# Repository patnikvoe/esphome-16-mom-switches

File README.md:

# esphome-16-mom-switches
create a pcb to be able to extend the use of homeassistant via esphome. Currently still a work in progress. Feedback welcome!

## components
- Seeedstudio Xiao ESP32C3
- MCP23017
- 10k resistor
- momentary push buttons
- array resistor
- 2x10 Male & Female header

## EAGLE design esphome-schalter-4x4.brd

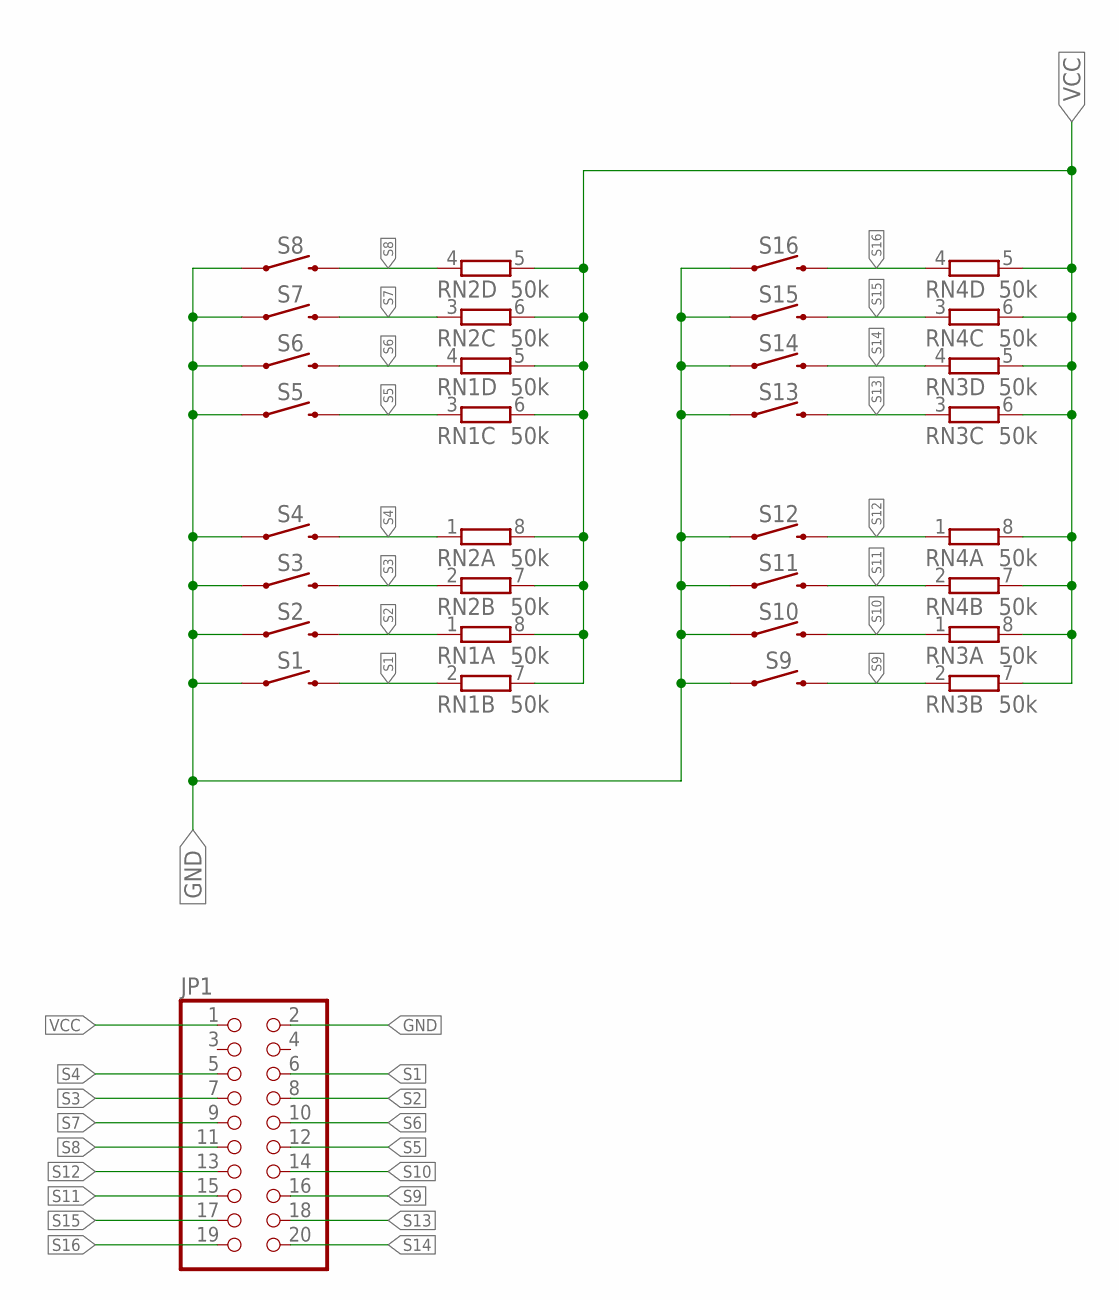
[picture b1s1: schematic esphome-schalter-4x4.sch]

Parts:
JP1: PINHD-2X10; 2X10
RN1, RN2, RN3, RN4: 50k; EXBS8V
S1, S2, S3, S4, S5, S6, S7, S8, S9, S10, S11, S12, S13, S14, S15, S16: MOMENTARY-SWITCH-SPST-PTH-6.0MM; TACTILE_SWITCH_PTH_6.0MM

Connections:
GND: JP1.2, S1.1, S2.1, S3.1, S4.1, S5.1, S6.1, S7.1, S8.1, S9.1, S10.1, S11.1, S12.1, S13.1, S14.1, S15.1, S16.1
S1: JP1.6, RN1.2 (1), S1.3 (2)
S2: JP1.8, RN1.1, S2.3 (2)
S3: JP1.7, RN2.2 (1), S3.3 (2)
S4: JP1.5, RN2.1, S4.3 (2)
S5: JP1.12, RN1.3 (1), S5.3 (2)
S6: JP1.10, RN1.4 (1), S6.3 (2)
S7: JP1.9, RN2.3 (1), S7.3 (2)
S8: JP1.11, RN2.4 (1), S8.3 (2)
S9: JP1.16, RN3.2 (1), S9.3 (2)
S10: JP1.14, RN3.1, S10.3 (2)
S11: JP1.15, RN4.2 (1), S11.3 (2)
S12: JP1.13, RN4.1, S12.3 (2)
S13: JP1.18, RN3.3 (1), S13.3 (2)
S14: JP1.20, RN3.4 (1), S14.3 (2)
S15: JP1.17, RN4.3 (1), S15.3 (2)
S16: JP1.19, RN4.4 (1), S16.3 (2)
VCC: JP1.1, RN1.5 (2), RN1.6 (2), RN1.7 (2), RN1.8 (2), RN2.5 (2), RN2.6 (2), RN2.7 (2), RN2.8 (2), RN3.5 (2), RN3.6 (2), RN3.7 (2), RN3.8 (2), RN4.5 (2), RN4.6 (2), RN4.7 (2), RN4.8 (2)

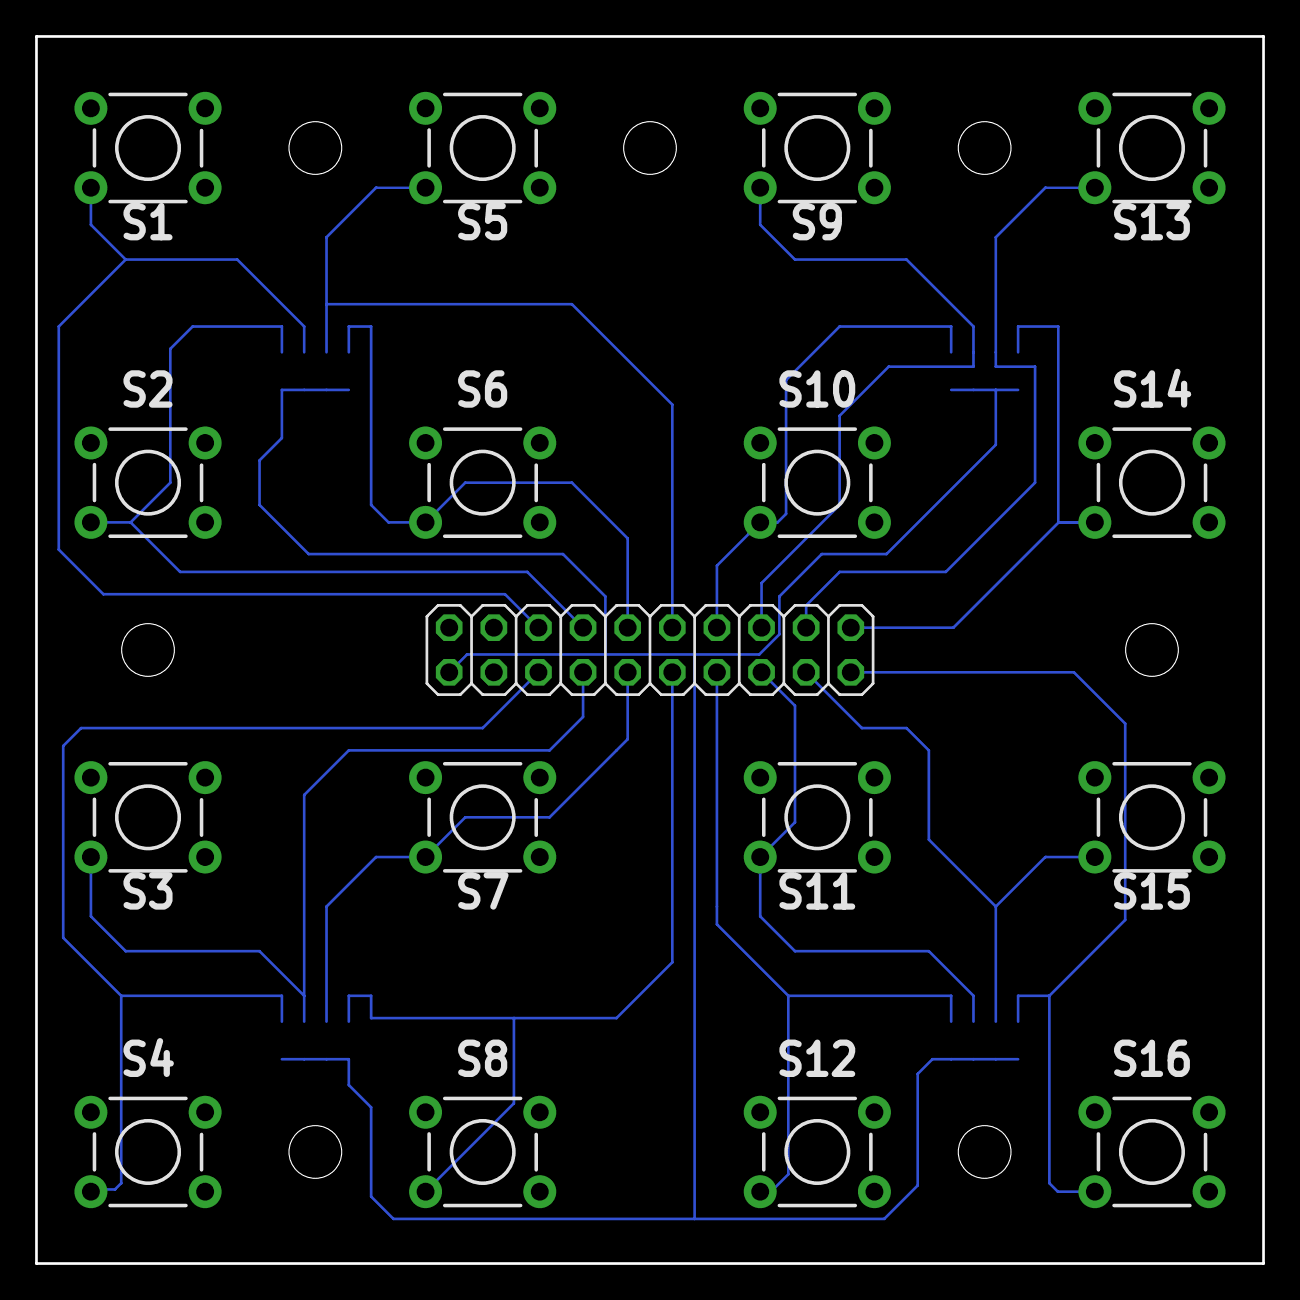
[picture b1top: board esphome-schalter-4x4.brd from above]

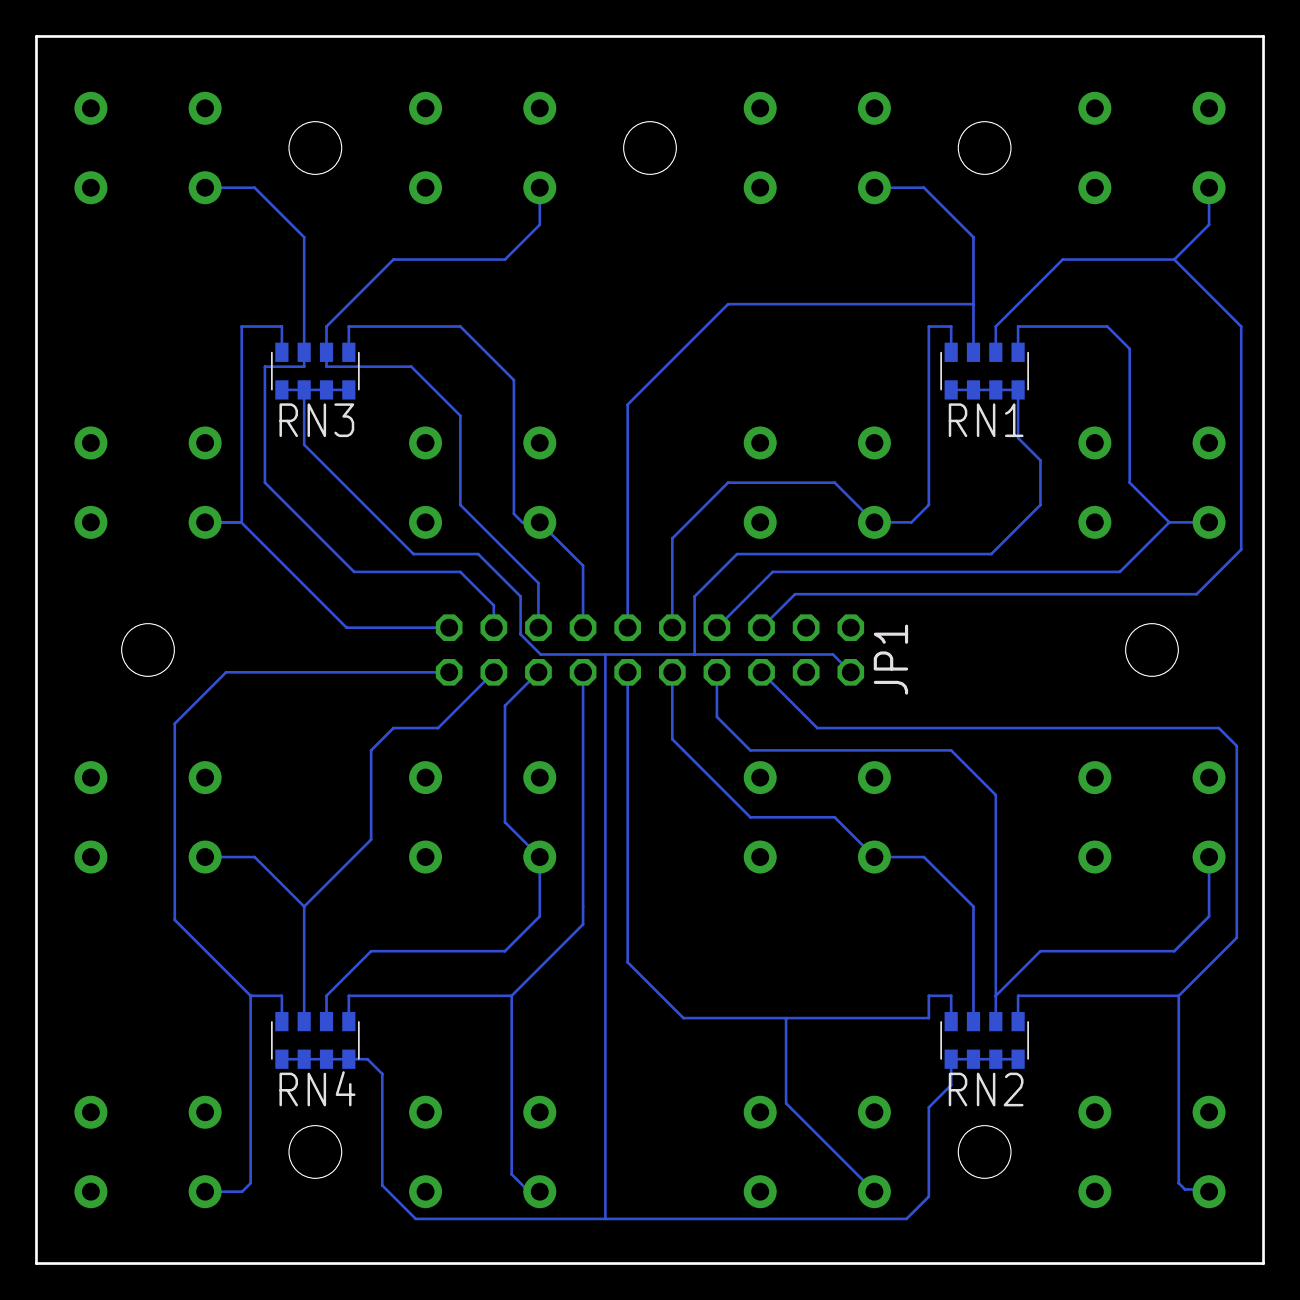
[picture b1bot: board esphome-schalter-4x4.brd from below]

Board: 2 copper layers, 69.8 x 69.8 mm, 21 parts (4 on the bottom side), 18 nets.

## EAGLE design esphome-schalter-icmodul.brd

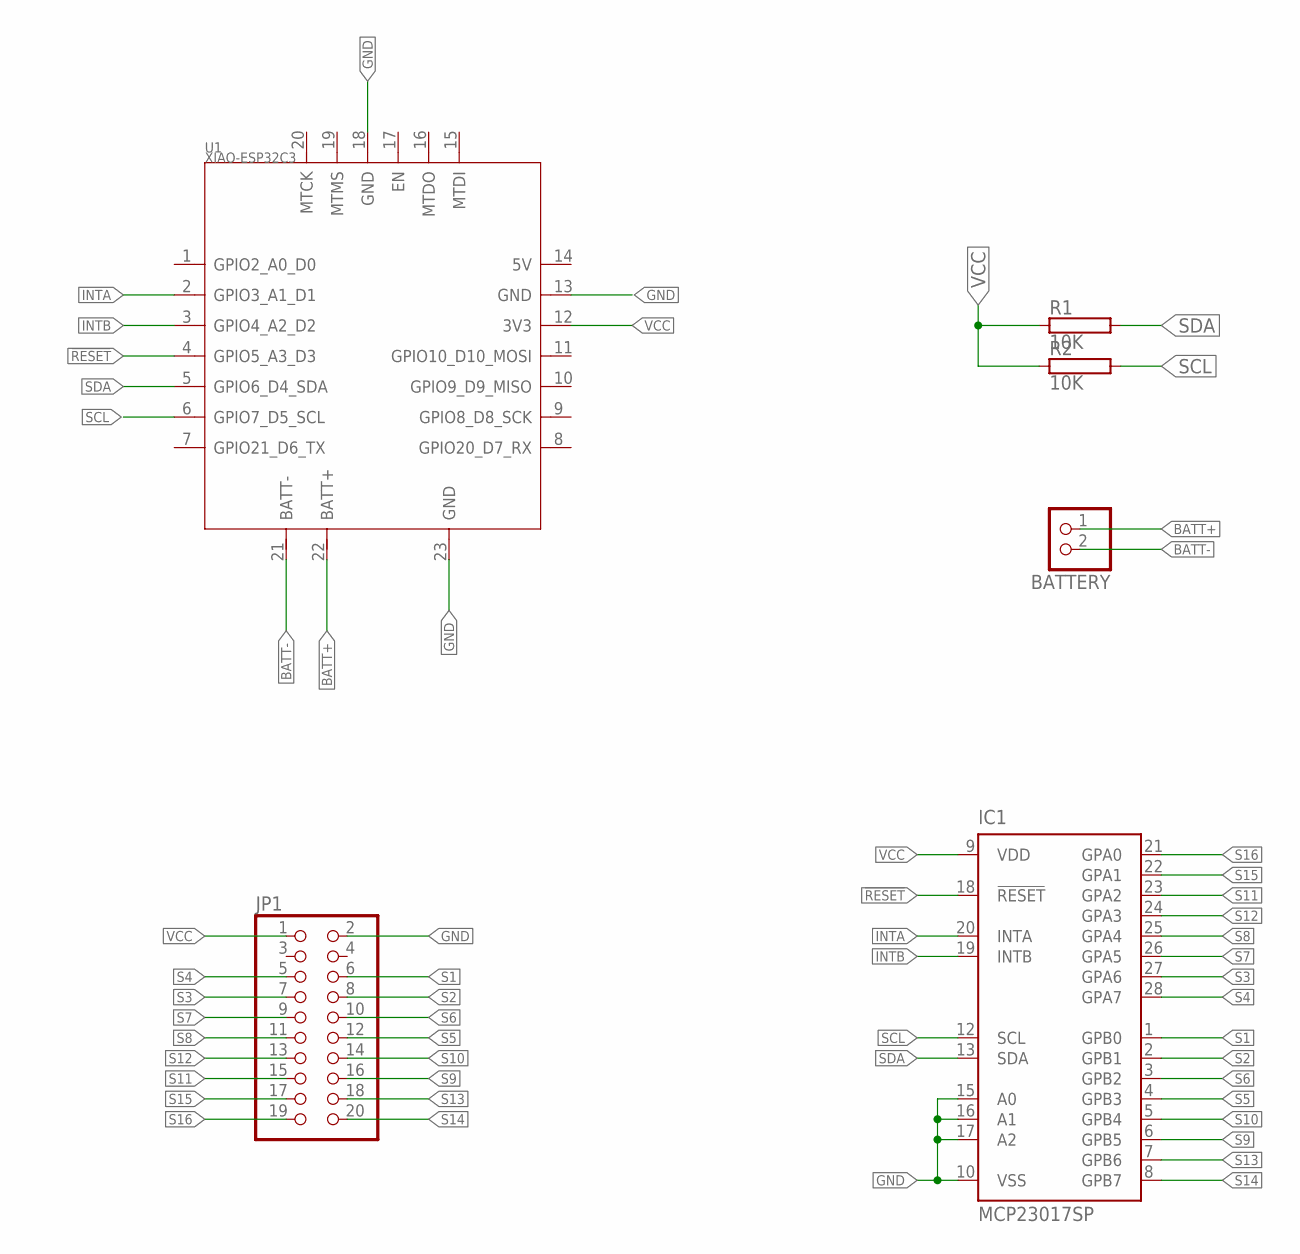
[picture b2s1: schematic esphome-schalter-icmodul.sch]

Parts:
BATTERY: JST_2PIN-SMT; JST-PH-2-SMT
IC1: MCP23017SP; DIL28-3
JP1: PINHD-2X10; 2X10
R1, R2: 10K; CA0001
U1: XIAO-ESP32C3; XIAO-ESP32C3-MODULE14P-2.54-21X17.8MM

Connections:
!RESET: IC1.18 (!RESET), U1.4 (GPIO5_A3_D3)
BATT+: BATTERY.1 (2), U1.22 (BATT+)
BATT-: BATTERY.2 (1), U1.21 (BATT-)
GND: IC1.10 (VSS), IC1.15 (A0), IC1.16 (A1), IC1.17 (A2), JP1.2, U1.13 (GND), U1.18 (GND), U1.23 (GND)
INTA: IC1.20 (INTA), U1.2 (GPIO3_A1_D1)
INTB: IC1.19 (INTB), U1.3 (GPIO4_A2_D2)
S1: IC1.1 (GPB0), JP1.6
S2: IC1.2 (GPB1), JP1.8
S3: IC1.27 (GPA6), JP1.7
S4: IC1.28 (GPA7), JP1.5
S5: IC1.4 (GPB3), JP1.12
S6: IC1.3 (GPB2), JP1.10
S7: IC1.26 (GPA5), JP1.9
S8: IC1.25 (GPA4), JP1.11
S9: IC1.6 (GPB5), JP1.16
S10: IC1.5 (GPB4), JP1.14
S11: IC1.23 (GPA2), JP1.15
S12: IC1.24 (GPA3), JP1.13
S13: IC1.7 (GPB6), JP1.18
S14: IC1.8 (GPB7), JP1.20
S15: IC1.22 (GPA1), JP1.17
S16: IC1.21 (GPA0), JP1.19
SCL: IC1.12 (SCL), R2.2, U1.6 (GPIO7_D5_SCL)
SDA: IC1.13 (SDA), R1.2, U1.5 (GPIO6_D4_SDA)
VCC: IC1.9 (VDD), JP1.1, R1.1, R2.1, U1.12 (3V3)

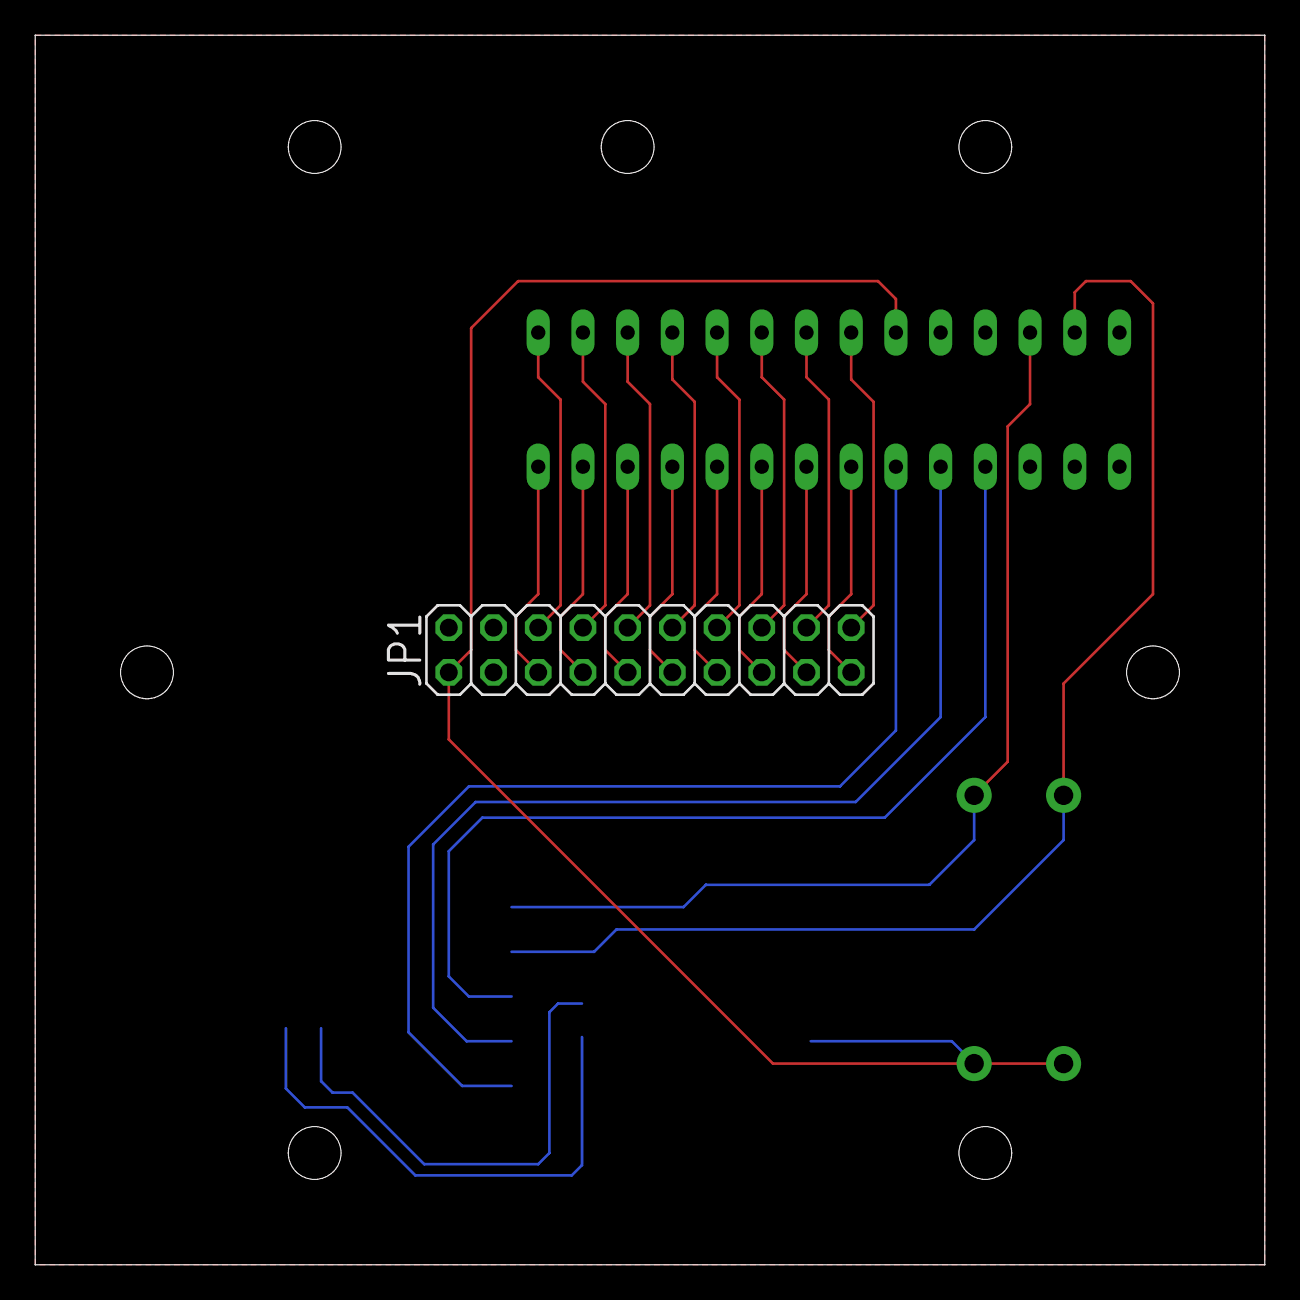
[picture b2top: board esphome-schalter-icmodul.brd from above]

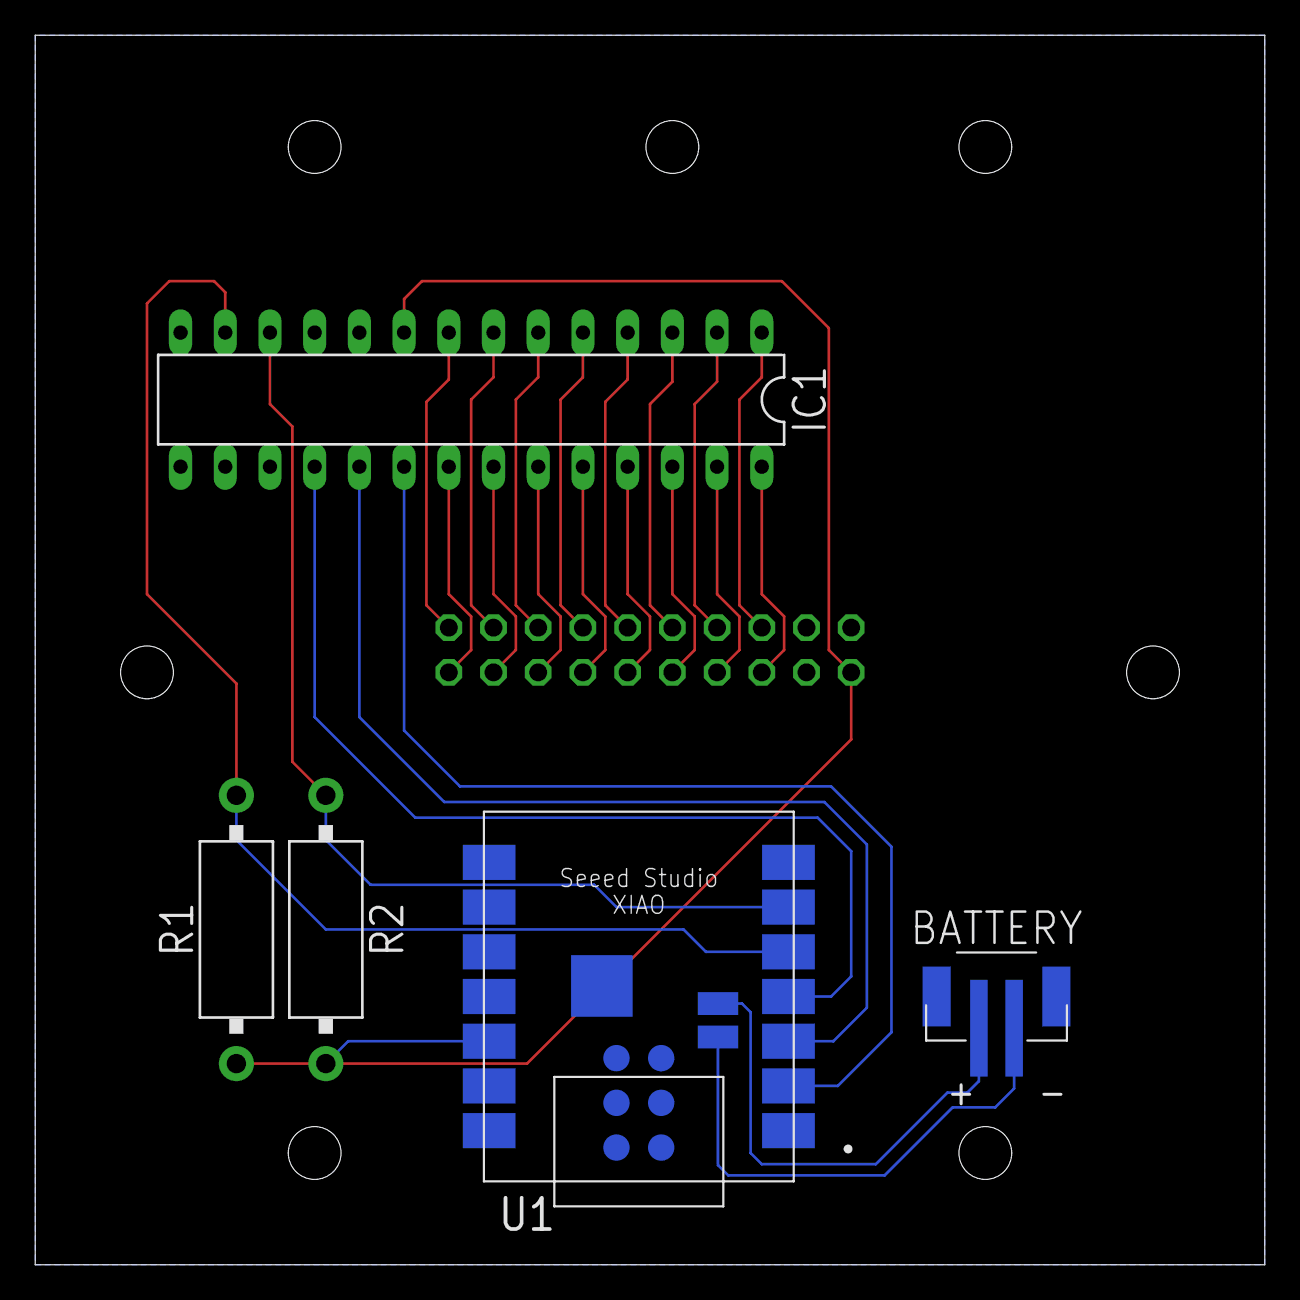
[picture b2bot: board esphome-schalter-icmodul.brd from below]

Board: 2 copper layers, 69.8 x 69.8 mm, 6 parts (5 on the bottom side), 25 nets.

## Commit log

2024-01-08 eagle project allowed
2024-01-08 create pdf of schematics
2024-01-08 added esphome config.yaml

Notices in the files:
parts and their libraries:
SparkFun-Switches: Licensing: Creative Commons ShareAlike 4.0 International - https://creativecommons.org/licenses/by-sa/4.0
